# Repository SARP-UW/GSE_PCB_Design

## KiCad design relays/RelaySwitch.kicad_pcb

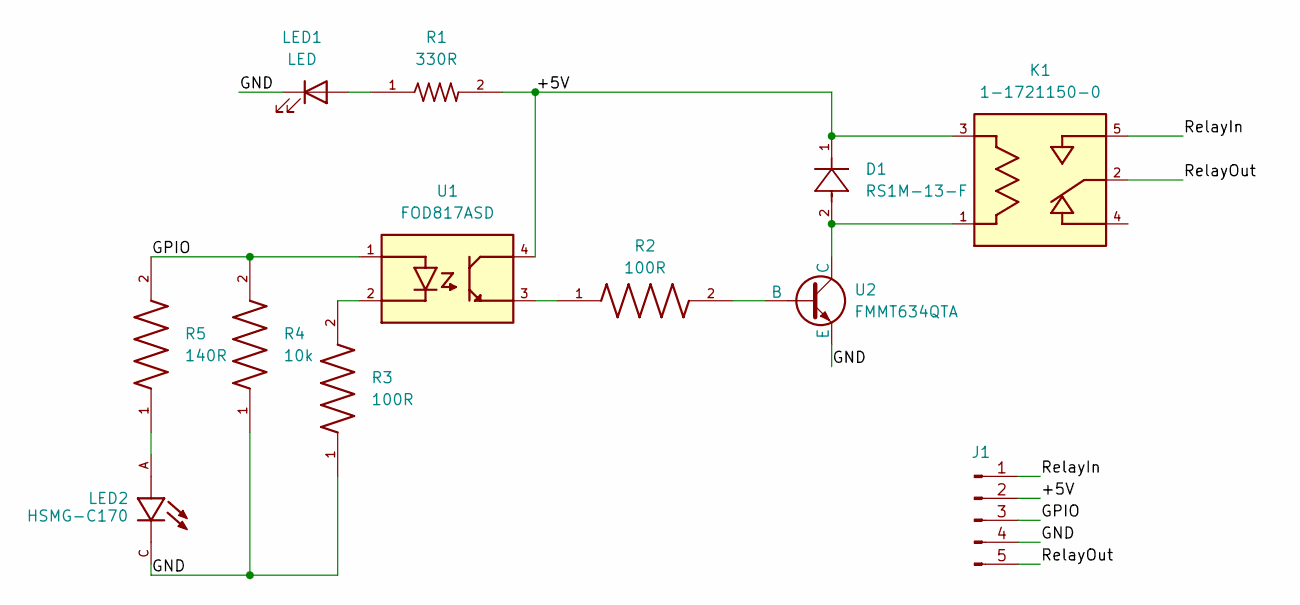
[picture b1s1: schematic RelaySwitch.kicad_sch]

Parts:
D1: RS1M-13-F; SMA_DIO-M; MANUFACTURER_PART_NUMBER RS1M-13-F
J1: Conn_01x05_Pin; PinHeader_1x05_P2.54mm_Vertical
K1: 1-1721150-0; RELAY_1-1721150-0; PARTREV D
LED1: LED; LED_SML-D12V1WT86
LED2: HSMG-C170; LED_HSMS-C170; PARTREV March 25, 2022
R1: 330R; RESC1607X60N
R2, R3: 100R; RESC1608X55N
R4: 10k; RESC1508X50N
R5: 140R; RESC1005X35N
U1: FOD817ASD; SOIC254P1016X385-4N
U2: FMMT634QTA; VREG_XC6206P282MR-G

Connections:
/+5V: D1.1, J1.2, K1.3, R1.2, U1.4
/GND: J1.4, LED1.1 (K), LED2.C, R3.1, R4.1, U2.3 (E)
/GPIO: J1.3, R4.2, R5.2, U1.1
/RelayIn: J1.1, K1.5
/RelayOut: J1.5, K1.2
unnamed: LED1.2 (A), R1.1
unnamed: LED2.A, R5.1
unnamed: R2.1, U1.3
unnamed: R3.2, U1.2
unnamed: R2.2, U2.2 (B)
unnamed: D1.2, K1.1, U2.1 (C)

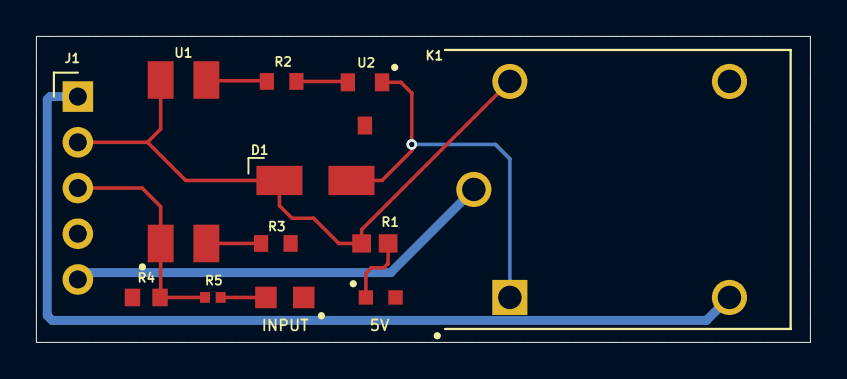
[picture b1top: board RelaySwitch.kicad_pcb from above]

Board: 2 copper layers, 43.0 x 17.0 mm, 12 parts (0 on the bottom side), 11 nets.

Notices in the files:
parts and their libraries:
COPYRIGHT: Copyright (C) 2023 Ultra Librarian. All rights reserved.
